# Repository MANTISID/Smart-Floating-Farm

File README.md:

# Smart-Floating-Farm
Future Farming Platform in Coastal and Remote Island. Cultivate the future, start from the sea. We submit this project to  Intel Hackathon 2017

## Inspiration
**We want to help people**

We see that local people in Coastal area and Remote Islands having difficulty in planting horticulture because they face the problem of land limitations. We have an idea about making floating platform so people can grow their vegetables at coastal area.
We inspired by [**GROASIS**](https://www.groasis.com/en), [**Seawater Greenhouse**](https://seawatergreenhouse.com/), and [**Hamster Ball-Shaped Solarball**](http://inhabitat.com/hamster-ball-shaped-solarball-uses-the-sun-to-purify-water/). They can grow plants at desert area and have a pure water using desalination process.
Hopefully this platform can help local people to reduce their dependence on supply from mainland, help them make their own food independence and also help to make more money from selling the harvest vegetables. We also can manage these process with supllying seed, provide consultation to user, and preparing the market to sell the vegetables.

## What it does
__**SMART FLOATING FARM (SFF) PLATFORM BUILD TO RECORD, MONITOR, AND MAKE DECISION BASED ON THE RECORD.**__

__**Initialize sensors and output**__

This platform will initialize serial, lcd, RTC (real time clock), sensors, and motor. If RTC cannot be detected, LCD will display error and user must fix it. After RTC is ok, Arduino101 will check communication with ESP8266. Arduino101 send "AT" and wait "OK" from ESP8266.
 
__**Get threshold from Server**__

After receiving "OK", Arduino will command ESP8266 as station mode and get parameter threshold from Server.  These threshold value used to ensure plants are in the range that has been determined by the user. SFF send GET method to server ([This link](http://mantisid.id/api/product/sff_th_r.php?Format=Sys) used to receive sensors threshold). Parameter threshold will be saved as variable.

__**Sensor Measurement**__

This platform record these parameters : soil moisture & temperature, greenhouse temperature & humidity, greenhouse smoke detection, vibration, plant height, time, and light intensity.
 
__**Sending Data to Server**__

Data from sensor compiled as String and send it to Web by ESP8266 using POST method ([Go to this link](http://mantisid.id/api/product/sff_dt_c.php) to send data to WebServer; [Visit this link](http://mantisid.id/api/product/sff_dt_r.php) to see data that received by WebServer from Platform).

__**Output Action**__

Arduino101 check data measurement with threshold received from Server. Based on these threshold, platform will give command automatically to activate LED indicator, water pump, exhaust fan and LED lamps based on sensors reading. After 10 seconds, platform will delay few minutes before the next measurement. While waiting, Arduino101 measure gyro value. 

## How we built it
We use Arduino IDE to built the firmware. We use libraries from internal Arduino IDE and from internet. For external library, we used  [SEEED RGB LCD ](https://github.com/Seeed-Studio/Grove_LCD_RGB_Backlight), [Adafruit DHT11 ](https://github.com/adafruit/DHT-sensor-library), [Adafruit RTC ](https://github.com/adafruit/RTClib), [Adafruit ADS1115 ](https://github.com/adafruit/Adafruit_ADS1X15), [MQ02 Gas Sensor](https://github.com/labay11/MQ-2-sensor-library), [Dallas DS18B20 ](https://github.com/milesburton/Arduino-Temperature-Control-Library), [Rotation from Gyro & Accelerometer](https://forum.arduino.cc/index.php?topic=378779.0), [Time Alarm ](https://github.com/michaelmargolis/arduino_time/tree/master/Time), and [Time Lib ](https://github.com/PaulStoffregen/Time). For internal library, we used Wire, pitches.h, CurieIMU and Software Serial. We used Mario Bros Tune developed by [Dipto Pratyaksa](http://www.linuxcircle.com/2013/03/31/playing-mario-bros-tune-with-arduino-and-piezo-buzzer/) to play sound at the beginning. IMU rotation angle we got from [Erikyo](https://forum.arduino.cc/index.php?topic=378779.0). SFF Arduino sketch can be found at [MANTIS GITHUB](https://github.com/MANTISID/Smart-Floating-Farm).

## Sensor and output configuration
**ARDUINO101   SENSOR/OUTPUT**
- D0    <---->    Tx UART
- D1    <---->    Rx UART
- D2    <---->    GREEN LED INDICATOR
- D3    <---->    RED LED INDICATOR
- D4    <---->    BUZZER
- D5    <---->    DHT11
- D6    <---->    SRF04 ECHO PIN
- D7    <---->    Tx ESP8266
- D8    <---->    Rx ESP8266
- D9    <---->    DS18B20
- D10   <---->    RELAY FOR EXHAUST FAN & SPRAYER
- D11   <---->    RELAY FOR WATER PUMP
- A0    <---->    VIBRATION SENSOR
- A1    <---->    LIGHT SENSOR
- A2    <---->    GREEN LED FOR LIGHTING
- A3    <---->    MQ02 GAS SENSOR

- A4    <---->    SDA
- A5    <---->    SCL

**I2C COMMUNICATION**
- RGB LCD SHIELD
- ADS1115 ADC 16 BIT
    * ADC1    <---->    SOIL MOISTURE SENSOR
    * ADC3    <---->    WATER LEVEL SENSOR
    
**INTERNAL USE:**
- INERTIAL MEASUREMENT UNIT (GYRO & ACCELEROMETER)

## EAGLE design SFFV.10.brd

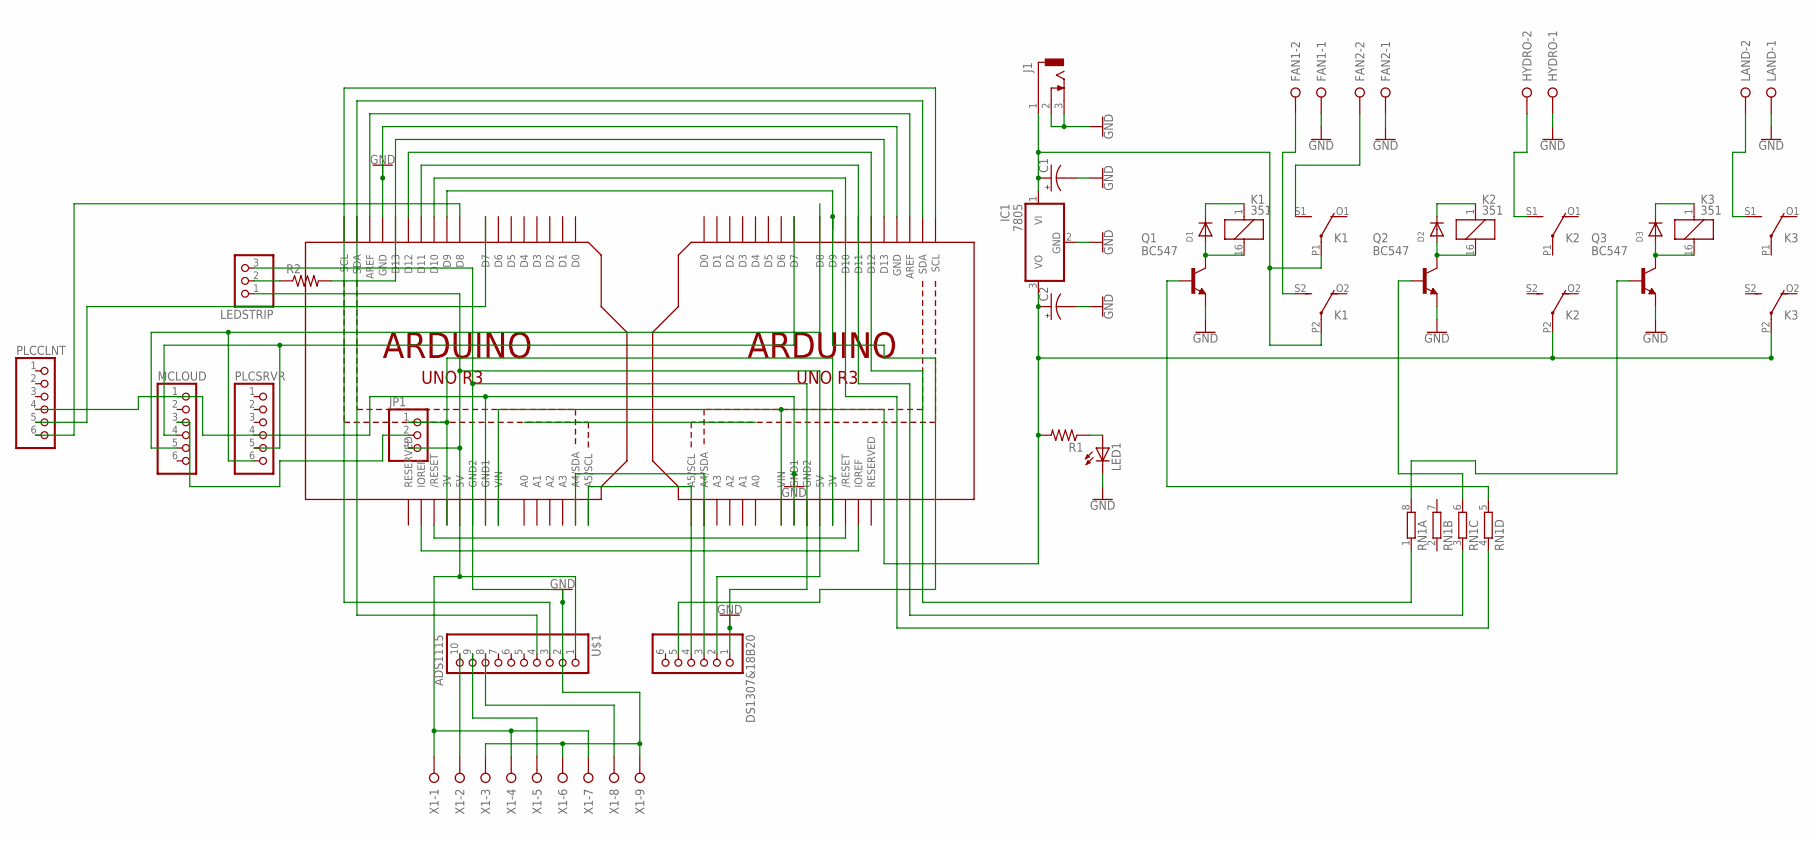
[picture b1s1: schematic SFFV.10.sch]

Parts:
C1, C2: CPOL-USE; PANASONIC_E
D1, D2, D3: DIODESMA; SMADIODE
DS1307&18B20: PINHD-1X6B; 1X06-BIG
FAN1, FAN2: W237-02P; W237-132
HYDRO: W237-02P; W237-132
IC1: 7805; TO220H
J1: DCJ0303
JP1: PINHD-1X3CB; 1X03-CLEANBIG
K1, K2, K3: 351
LAND: W237-02P; W237-132
LED1: LED5MM
LEDSTRIP: PINHD-1X3; 1X03
MCLOUD: PINHD-1X6B; 1X06-BIG
PLCCLNT: PINHD-1X6B; 1X06-BIG
PLCSRVR: PINHD-1X6B; 1X06-BIG
Q1, Q2, Q3: BC547; TO92
R1, R2: R-US_MELF0207W; MINI_MELF-0207W
RN1: 4R-NEXB38V; EXB38V
U1, U2: ARDUINOR3-BPLACE
U$1: ADS1115; 1X10-BIG
X1: W237-09P; W237-9P

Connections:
GND: C1.-, C2.-, DS1307&18B20.1, FAN1.1, FAN2.1, HYDRO.1, IC1.2 (GND), J1.2, J1.3, LAND.1, LED1.K (C), LEDSTRIP.3, MCLOUD.1, PLCCLNT.4, PLCSRVR.4, Q1.1 (E), Q2.1 (E), Q3.1 (E), U1.GND, U1.GND1, U1.GND2, U2.GND, U2.GND1, U2.GND2, U$1.2, X1.3, X1.6, X1.9
unnamed: LEDSTRIP.2, R2.1
unnamed: LED1.A, R1.1
unnamed: MCLOUD.4, PLCSRVR.5, U2.D7
unnamed: JP1.2, MCLOUD.3
unnamed: PLCCLNT.5, U1.D7
unnamed: DS1307&18B20.4, U1.A5 (A5/SCL), U2.A5 (A5/SCL)
unnamed: DS1307&18B20.3, U1.A4 (A4/SDA), U2.A4 (A4/SDA)
unnamed: MCLOUD.5, PLCSRVR.6, U2.D8
unnamed: JP1.1, U1.3V, U2.3V
unnamed: U1.RESET (/RESET), U2.RESET (/RESET)
unnamed: U1.IOREF, U2.IOREF
unnamed: PLCCLNT.6, U1.D8
unnamed: DS1307&18B20.5, U1.D9, U2.D9
unnamed: RN1.4 (1), U1.D10, U2.D10
unnamed: RN1.3 (1), U1.D11, U2.D11
unnamed: RN1.1, U1.D12, U2.D12
unnamed: R2.2, U1.D13, U2.D13
unnamed: U1.AREF, U2.AREF
unnamed: U1.SDA, U2.SDA, U$1.4
unnamed: U$1.10, X1.2
unnamed: C1.+, IC1.1 (VI), J1.1, K1.P1, K1.P2
unnamed: C2.+, IC1.3 (VO), K2.P2, K3.P2, R1.2, U1.VIN, U2.VIN
unnamed: Q1.2 (B), RN1.5 (2)
unnamed: Q2.2 (B), RN1.6 (2)
unnamed: HYDRO.2, K2.S1 (S)
unnamed: Q3.2 (B), RN1.8 (2)
unnamed: D1.A, K1.16 (2), Q1.3 (C)
unnamed: D1.C, K1.1
unnamed: D2.A, K2.16 (2), Q2.3 (C)
unnamed: D2.C, K2.1
unnamed: D3.A, K3.16 (2), Q3.3 (C)
unnamed: D3.C, K3.1
unnamed: FAN2.2, K1.S1 (S)
unnamed: FAN1.2, K1.S2 (S)
unnamed: K3.S1 (S), LAND.2
unnamed: U$1.9, X1.5
unnamed: U$1.8, X1.8
unnamed: U1.SCL, U2.SCL, U$1.3
PLCCLNT: DS1307&18B20.2, JP1.3, LEDSTRIP.1, U1.5V, U2.5V, U$1.1, X1.1, X1.4, X1.7

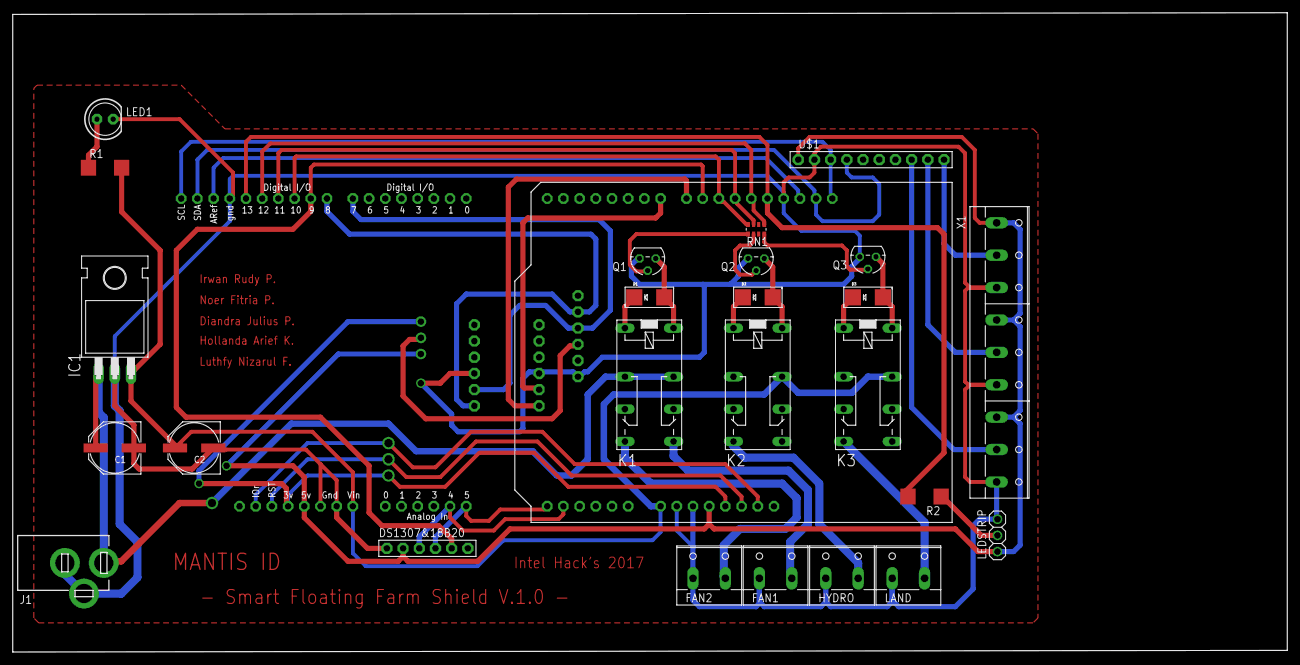
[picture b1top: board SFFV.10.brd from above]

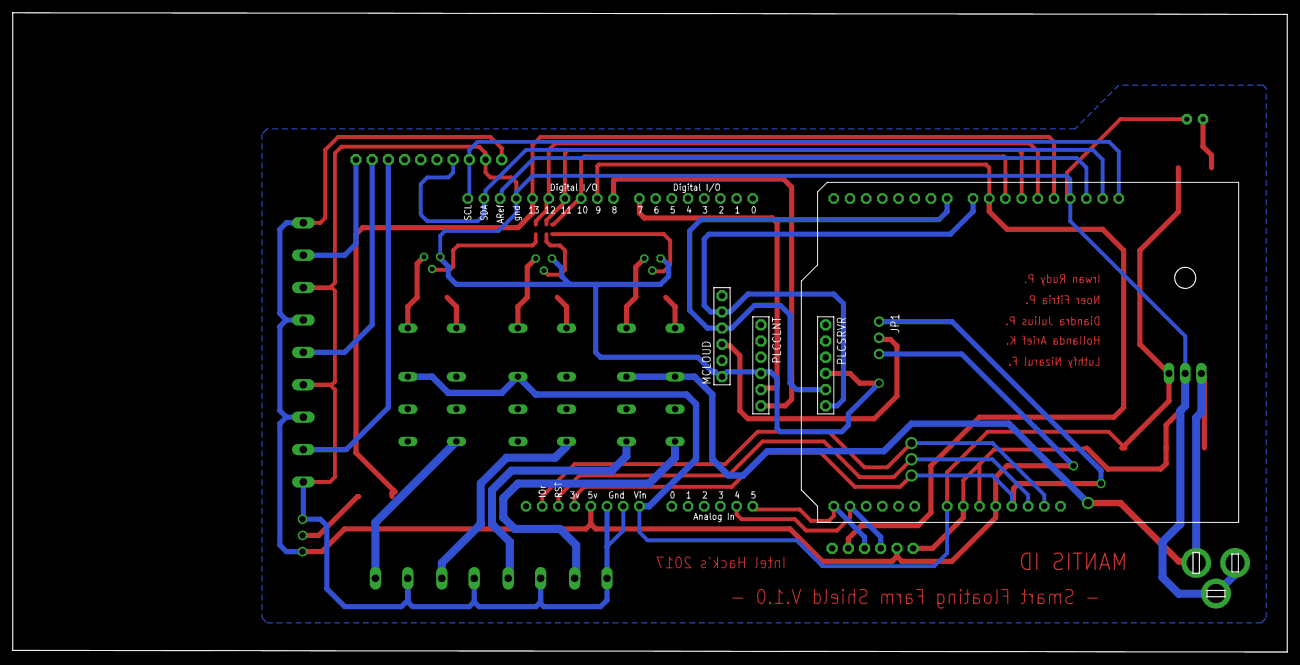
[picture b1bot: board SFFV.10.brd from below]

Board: 2 copper layers, 199.9 x 100.3 mm, 31 parts (5 on the bottom side), 40 nets.

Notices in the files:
parts and their libraries:
SparkFun-PowerSymbols: Licensing: Creative Commons ShareAlike 4.0 International - https://creativecommons.org/licenses/by-sa/4.0
